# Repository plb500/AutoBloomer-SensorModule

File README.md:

# AutoBloomer Sensor Modules

Full plans and code for a sensor controller capable of publishing multiple sensor data via MQTT

Raspberry Pico source code is [here](pico/src)

PCB schematics (KiCad format), plans plus any 3D prints/CNC files for the different hardware platforms are [here](hardware)

A brief overview is on [YouTube](https://youtu.be/QP_2SgASPRE)

Under the hood the sensor modules use Raspberry Pico Ws to communicate with an MQTT broker and transmit data it collates from the following sensors:
- SCD30 environmental sensor ([link](https://www.sensirion.com/products/catalog/SCD30/))
- Stemma soil sensor ([link](https://www.adafruit.com/product/4026))
- Battery voltage (for Raspberry Pi RTC) (uses an ADC pin on the Pico and custom circuitry on the HIB)
- Sonar (feed level) sensors (Currently using A02YYUW sonars - [link](https://www.dfrobot.com/product-1935.html))

I also intend to add EC and/or pH sensors to this to essentially make this a one-stop hydroponics sensor interface.

The module arranges these sensors into sensor "groups", referred to by their index. Each group effectively publishes a set of data from multiple sensors to a single MQTT topic. This allows the Sensor Pod, for example, to accumulate sensor data from both the SCD30 sensor and the Stemma Soil Sensor into a single topic, and also allows the HIB to publish sensor data to multiple topics (i.e. the RTC battery voltage and each individual connected feed sensor all publish to their own individual topics)

## Hardware platforms
Currently there are two different hardware platforms defined:
- Sensor Pod
- Hardware Interface Board (HIB)

### Sensor Pod
The Sensor Pod consists of a single sensor group providing data from the following sensors:
- Group 0
  - SCD30
    - CO2
    - Humidity
    - Temperature
  - Stemma Soil Sensor
    - Soil moisture
 
### Hardware Interface Board
The HIB consists of two distinct pieces of hardware. One section provides power and hardware control to the Raspberry Pi powering the [AutoBloomer controller](https://github.com/plb500/AutoBloomer-Controller), along with a RTC module and interfacing to relays. The other section is the sensor module which provides data from feed level sensors along with the current RTC battery module voltage. These are grouped as follows:
- Group 0
  - RTC battery level
- Group 1
  - Feed sensor
- Group 2
  - Feed sensor
 
## Module configuration
Configuration of each module is done in two ways:

### Basic module configuration
Basic pod configuration of essential runtime variables (wireless SSID/key, broker address, module location/name etc) is done via serial port connected to the bord's EXT header (3.3v, 57600/8/n/1) and transmitting commands in the format: `<COMMAND><SENSOR_GROUP><PARAMETER>` (note no space)
- SSID<< wireless ssid >> - Sets the WiFi SSID
- PASS<< password >> - Sets WiFi passkey
- NAME<< module >> - Sets sensor module name
- BRKR<< address >> - Sets the broker address
- GRPN<< sensor group index>><< sensor group name >> - Sets the name of the sensor group at the supplied index (this is used for the MQTT topic path)
- GRPL<<sensor group index>><< sensor group location >> - Sets the location of the sensor group at the supplied index (this is used for the MQTT topic path)

#### Example commands
- `SSIDMyNetwork` -> Sets the sensor module to connect to the wireless network with the SSID "MyNetwork"
- `PASSthe_key` -> Sets the sensor module to connect to the wireless network using the PSK "the_key"
- `NAMESensorModule` -> Sets the Pico's host/MQTT client name to be "SensorModule"
- `BRKRthebroker.local` -> Tells the sensor module to connect and publish to the MQTT broker with host name "thebroker.local"
- `BRKR192.168.1.50` -> Tells the sensor module to connect and publish to the MQTT broker at address "192.168.1.50"
- `GRPN0Group1Sensor` -> Sets the name of the sensor group at index 0 to "Group1Sensor"
- `GRPL0LeftChamber` -> Sets the location of the sensor group at index 0 to "LeftChamber"

Once these have been set the pod will attempt to connect to the configured broker via the supplied wireless network and begin publishing sensor data to the topic:

```
AutoBloomer/<< sensor group location >>/<< sensor group name >>
```

### Runtime sensor calibration
Once connected, the pod will also subscribe to a specific MQTT topic to listen for sensor calibration commands. The topic in question is:
```
AutoBloomer/<< sensor group location >>/<< sensor group name >>/control
```

The payload consists of a single line detailing the type of calibration to be performed. Currently the only sensor capable of (and requiring) calibration is the SCD30 on the Sensor Pod.
Calibration commands are one of the following:
- TEMP (temperature offset)
- FRC (CO2 field calibration value)

For example, setting a FRC value of 400 (i.e. recalibrating outside) and using mosquitto_pub the command line would look something like this:

```
mosquitto_pub -h broker.address -m "FRC 400" -t "AutoBloomer/SensorLocation/SensorName/control"
```

For more details on these parameters, see the SCD30 documentation [here](/docs/SCD30_Interface_Description.pdf)

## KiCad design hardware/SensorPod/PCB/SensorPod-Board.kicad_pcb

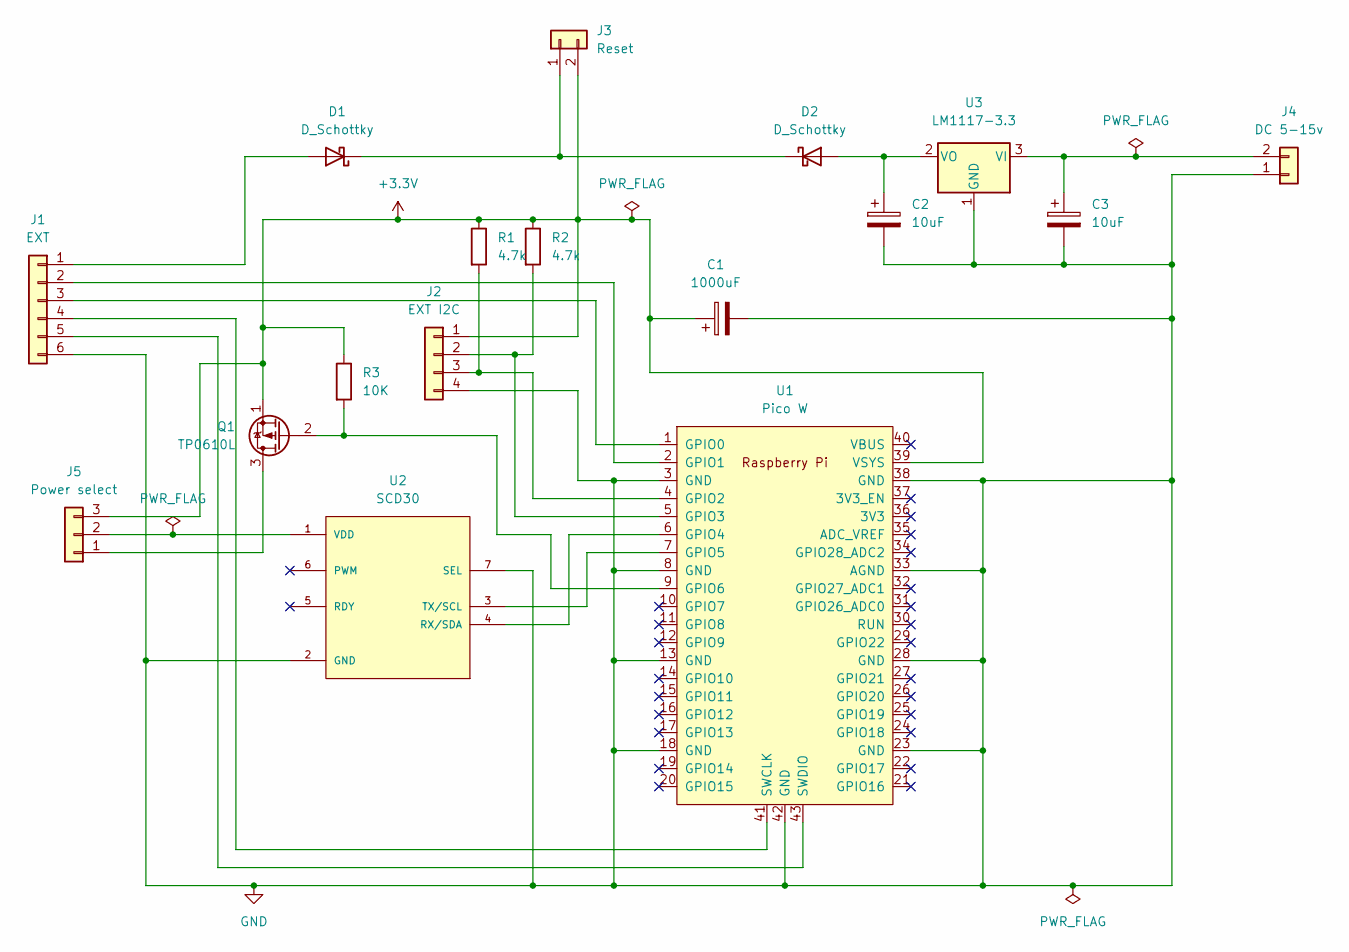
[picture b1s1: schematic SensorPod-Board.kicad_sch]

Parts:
C1: 1000uF; CP_Radial_D12.5mm_P5.00mm
C2, C3: 10uF; C_Radial_D6.3mm_H5.0mm_P2.50mm
D1, D2: D_Schottky; D_DO-35_SOD27_P7.62mm_Horizontal
J1: EXT; JST_XH_B6B-XH-A_1x06_P2.50mm_Vertical
J2: EXT I2C; JST_XH_B4B-XH-A_1x04_P2.50mm_Vertical
J3: Reset; JST_XH_B2B-XH-A_1x02_P2.50mm_Vertical
J4: DC 5-15v; JST_XH_B2B-XH-A_1x02_P2.50mm_Vertical
J5: Power select; PinHeader_1x03_P2.54mm_Vertical
Q1: TP0610L; TO-92L_Inline
R1, R2: 4.7k; R_Axial_DIN0207_L6.3mm_D2.5mm_P7.62mm_Horizontal
R3: 10K; R_Axial_DIN0207_L6.3mm_D2.5mm_P7.62mm_Horizontal
U1: Pico W; RPi_Pico_SMD_TH
U2: SCD30; MODULE_SCD30; PARTREV D1
U3: LM1117-3.3; TO-220-3_Horizontal_TabDown

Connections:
+3.3V: C1.1, J2.1, J3.2, J5.3, Q1.1 (S), R1.1, R2.1, R3.1, U1.39 (VSYS)
GND: C1.2, C2.2, C3.2, J1.6, J2.4, J4.1, U1.3 (GND), U1.8 (GND), U1.13 (GND), U1.18 (GND), U1.23 (GND), U1.28 (GND), U1.33 (AGND), U1.38 (GND), U1.42 (GND), U2.2 (GND), U2.7 (SEL), U3.1 (GND)
unnamed: C2.1, D2.2 (A), U3.2 (VO)
unnamed: C3.1, J4.2, U3.3 (VI)
unnamed: D1.1 (K), D2.1 (K), J3.1
unnamed: D1.2 (A), J1.1
unnamed: J1.2, U1.2 (GPIO1)
unnamed: J1.3, U1.1 (GPIO0)
unnamed: J1.4, U1.41 (SWCLK)
unnamed: J1.5, U1.43 (SWDIO)
unnamed: J2.2, R2.2, U1.5 (GPIO3)
unnamed: J2.3, R1.2, U1.4 (GPIO2)
unnamed: J5.1, Q1.3 (D)
unnamed: J5.2, U2.1 (VDD)
unnamed: Q1.2 (G), R3.2, U1.9 (GPIO6)
unnamed: U1.6 (GPIO4), U2.4 (RX/SDA)
unnamed: U1.7 (GPIO5), U2.3 (TX/SCL)

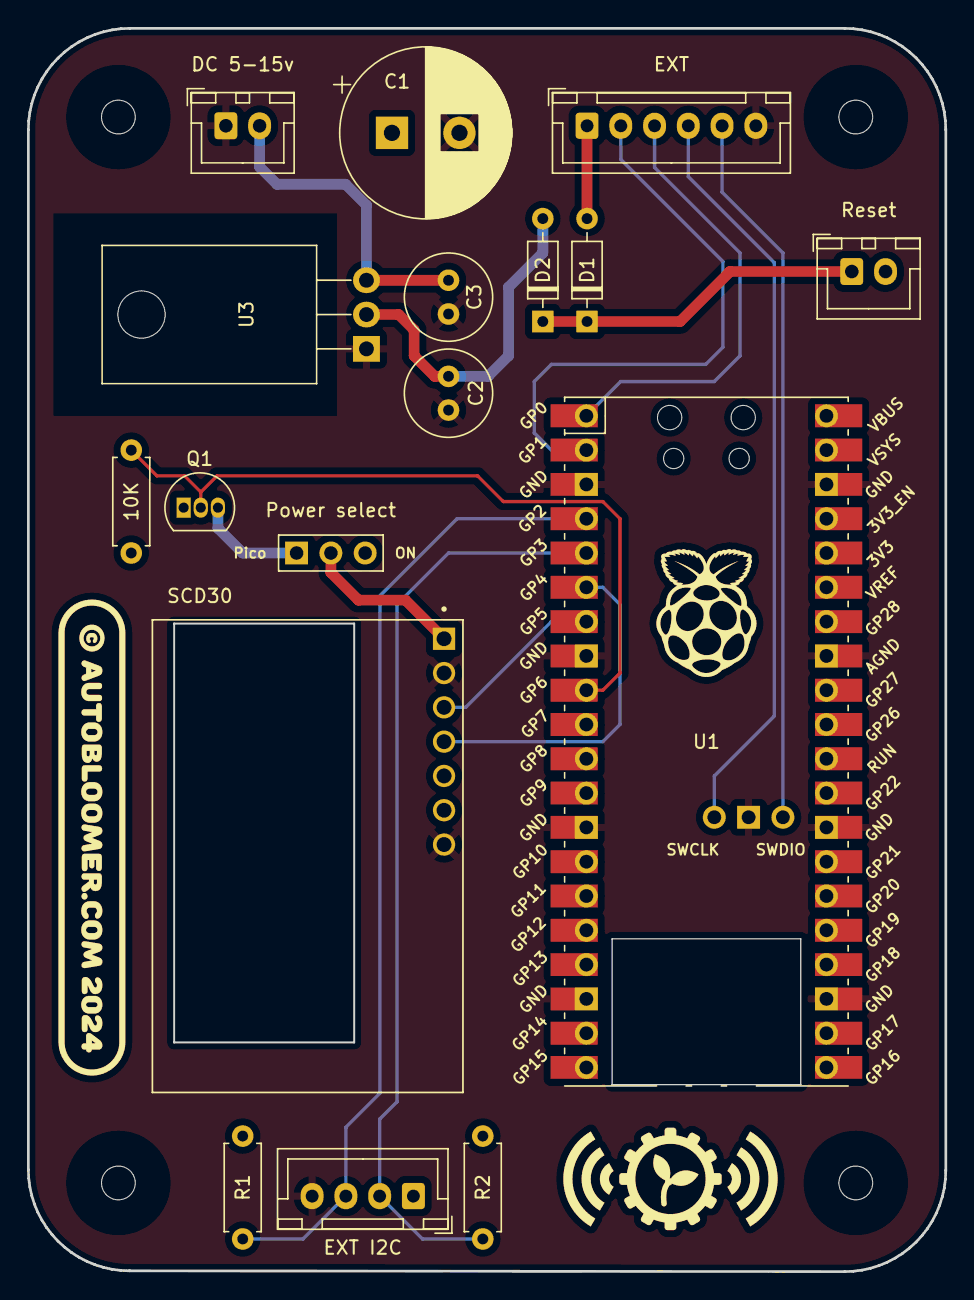
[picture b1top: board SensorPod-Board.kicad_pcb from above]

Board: 2 copper layers, 67.9 x 92.1 mm, 17 parts (0 on the bottom side), 17 nets.

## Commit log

2023-03-13 Initial code push. Everything is working but could be organized better
2023-03-13 Making things a bit cleaner
2023-03-15 Created wrapper struct for sensor pod
2023-03-16 Putting individual sensor (stemma/scd30) functions behind a single interface header
2023-03-16 Just hacking in some prototype code for testing the shift register
2024-01-19 Tidying up repo in preparation for new board
2024-01-19 Massive hackdump. Have network settins stored in a custom flash area via linker script. Simple serial utility to set the values. Networking and MQTT running on core0. Core1 active but not doing anyth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
2024-01-20 More hackery, MQTT connection and updating is working. Code is a mess
2024-01-20 Code is a bit cleaner. Need to wrap print functions still but everything is pretty functional
2024-01-21 Board fixes
2024-01-21 Switched over to using the actual Sensirion driver and providing a hal implementation. Tidied up a ton of code, fixed some weird behaviour. Better check it in before I fix everything beyond all repair
2024-01-25 Fixing up some sensor watchdog bugs and switching to a controlled log print system
2024-01-29 Fixing up debug printing
2024-01-29 Better board version. Power cycling of sensor controlled by Pico.
2024-01-30 Setting calibration values for SCD30 via MQTT (currently disabled until I get braver)
2024-01-30 Tidying up core messaging stuff a bit, everything was spread out everywhere. It's still mroe spread out than I would like but this at least is better
2024-01-31 More logging. Harder resetting. Basically all I can do now with a MOSFET to physically power cycle the SCD30
2024-02-04 Added some more network data debugging
2024-02-04 README images
2024-02-11 Going to let the underlyng libraries handle timeouts/disconnects and just react to them.
2024-02-12 Mass bulk conversion of all C files to C++ classes. Haven't verified anything works yet
2024-02-12 MQTT/networking/multicore SEEMS to be working
2024-02-12 Sensors on core1 seem to be processing and correctly communicating to core0. MQTT transmission succeeds
2024-02-12 Sensor calibration commands functional again. Everything now seems to be working in C++. Probably some horrible bugs lurking somewhere but I'll get to those later
2024-02-12 Converted entire codebase over to C++. (#2)
    * Mass bulk conversion of all C files to C++ classes. Haven't verified anything works yet
    * MQTT/networking/multicore SEEMS to be working
    * Sensors on core1 seem to be processing and correctly communicating to core0. MQTT transmission succeeds
    * Sensor calibration commands functional again. Everything now seems to be working in C++. Probably some horrible bugs lurking somewhere but I'll get to those later
2024-02-12 Clearing out all the old C code
2024-02-12 A wild space appears
2024-02-18 Checkpoint commit - first steps towards full sensor inheritance hierarchy and allowing sensor groups to be compile-time defined
2024-02-18 Sensor Pod sensors (+multiple sensors in group) working
2024-02-18 Big refactor to unbind this from SensorPod implementation
2024-02-18 OK, fixed up MQTT control messages. Made the scanning mroe robust and unable to be overflowed
2024-02-18 Bit of cleanup, sprinkling of some debug output.
2024-02-19 Adding more sensor types
2024-02-19 Setting name/location per sensor group (so they can each have their own topic)
2024-02-20 Refactored so MQTT topics are set on a per-group basis. Need to handle incoming MQTT messages
2024-02-20 Fixed up MQTT control messages
2024-02-20 Fixing up SensorPod hardware config
2024-02-20 Restructuring project to include PCB/hardware designs from multiple boards (since all will be based off this repo now)
2024-02-20 Tidying up SensorPod board project directory
2024-02-21 Having cmake control the compilation for different hardware platforms directly. This is much better.
2024-02-22 Fixing up remaining sensors for HIB
2024-02-22 Images and docs
2024-02-22 Fixed up paths for extra device symbols/models. Swapped HIB design over to Pico W footprint
2024-02-22 PCB renders
2024-02-22 Update README.md
    Typo
2024-02-22 Housekeeping - cleaning up sensor source folder structure
2024-02-22 Forgot to buil SensorPod type. Fixed.
2024-02-23 Hooking in connection detect/indicate functionality for HIB
2024-02-25 Using newest pico/debugprobe code
2024-02-25 Switching to Sensirion bitbang I2C library. At this point I'm convinced something is up with the Pico I2C lib
2024-02-25 Adding onboard LED indicator wrapper for different hardware platforms
2024-02-28 Update README.md
    Updated video link
2024-03-03 Fixing MQTT JSON output and adding config for new debug probe
2024-03-09 Switching to my own queue implementation with mutex. Fixing up openocd program script. Cleaning up some mess in the repo
2024-03-12 External WiFi LED indicator for HIB
2024-03-12 Fixing up some Pico bugs, new debugprobe setup
2024-03-16 Cleaning up directories and adding NOSTOP as a member to the Pico I2C wrapper (going to try going back to non-bitbang for SCD30)
2024-03-17 Moving code around and consolidating sensirion interfaces to try and switch between bitbang and pic h2 I2c comms
2024-03-17 Compile time configuration of underlying I2C implementation
2024-03-17 CMake bug
2024-03-17 Don't need the sample program
2024-03-17 Merging bitbang branch to main (#3)
    * Switching to Sensirion bitbang I2C library. At this point I'm convinced something is up with the Pico I2C lib
    * Switching to my own queue implementation with mutex. Fixing up openocd program script. Cleaning up some mess in the repo
    * Cleaning up directories and adding NOSTOP as a member to the Pico I2C wrapper (going to try going back to non-bitbang for SCD30)
    * Moving code around and consolidating sensirion interfaces to try and switch between bitbang and pic h2 I2c comms
    * Compile time configuration of underlying I2C implementation
    * CMake bug
2024-03-20 Fixing some allocation and iniialization bugs. Enabling configuration of SCD30
2024-03-20 Scale soil moisture between 0-100
2024-06-28 Fixing up launch parameters for linux host. Fixing serial processor
2024-08-10 Fixing up/making nicer debug output. Fixed issue with sensors not responding to MQTT control commands
2024-12-01 Add MQTT timeout and tidy up log output
2024-12-01 Exclude KiCad auto-backups
2024-12-15 Making repo compatible with new VSCode Pico plgin and hopefully making the connectin monitoring a bit cleaner/more stable
